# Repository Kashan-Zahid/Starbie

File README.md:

# Starbie

Starbie is a custom electronics project built around a designed PCB, firmware, and a 3D-printed enclosure. The project combines circuit design, component integration, embedded programming, and enclosure modelling into one compact device.

## Circuit Design

The circuit schematic and PCB layout were designed using KiCad. The schematic defines the electrical connections, while the PCB layout arranges the components and their connections on the board.

## Casing Design

I designed a custom 3D-printed enclosure to house and protect the electronics. The casing went through design revisions to improve its appearance and fit with the PCB.

## Why I Made It

I wanted to challenge myself to develop a hardware project from scratch and combine electronics, PCB design, firmware, and 3D modelling. This project gave me an opportunity to work through the process of turning a circuit design into a physical product.

## Features and Operation

- Custom PCB designed in KiCad.
- Electronic components integrated onto the board.
- Custom 3D-printed enclosure.
- Tactile buttons for user input.
- USB-C power connection, if supported by the final assembled design.

Refer to the final firmware and schematic for the exact functions supported by the completed device.

## Assembly Instructions

### 1. Review the design files

Open the KiCad schematic (`.kicad_sch`) and PCB layout (`.kicad_pcb`). Review the component positions, footprints, and electrical connections before assembly.

### 2. Prepare the PCB

Export the Gerber and drill files from KiCad if the board will be manufactured by a PCB fabrication service. Check the manufacturing outputs before submitting them.

### 3. Gather the components

Use the BOM to identify the required components, quantities, and package types. Confirm that each component matches the footprint and electrical specifications in the schematic.

### 4. Assemble the electronics

Place each component according to the PCB silkscreen, schematic, and component polarity markings. Solder the components that require soldering, checking for solder bridges and incorrect orientations.

### 5. Inspect the assembled board

Before applying power, inspect the solder joints and verify the power connections. Check for shorts between power and ground with a multimeter.

### 6. Install the firmware

Use the firmware files included in the repository and follow the programming instructions for the microcontroller used in the final design. Confirm that the firmware matches the hardware and required pin assignments.

### 7. Test the electronics

Power the board using its specified supply voltage. Test the display, sensors, buttons, and other connected components individually, then verify that they work together as intended.

### 8. Fit the enclosure

Place the tested PCB into the 3D-printed casing. Check the alignment of the display, buttons, connectors, and mounting points. Make any necessary adjustments before final assembly.

**Note:** These are general assembly steps. Exact soldering locations, firmware commands, pin assignments, and mounting instructions should be added from the final hardware and firmware files.

## Challenges I Faced

Designing the PCB and creating a casing that fits the electronics required careful planning and revisions. I improved the PCB layout after reviewing the earlier design and worked on redesigning the enclosure to achieve a better fit and appearance. Preparing manufacturing files also helped me understand how a digital PCB design becomes a physical board.

## What I Learned

- Designing electronic schematics and PCB layouts using KiCad.
- Organising components and checking footprints.
- Preparing PCB manufacturing files.
- Designing and revising a 3D-printed enclosure.
- Planning the integration of electronics, firmware, and physical components.

## Bill of Materials (BOM)

The following table lists the component prices previously recorded for the project. Prices and availability must be confirmed against the linked product listings before they are treated as verified current prices.

| Component | Quantity | Supplier | Unit price (USD) | Line total (USD) |
|---|---:|---|---:|---:|
| DHT11 temperature and humidity sensor | 1 | [Circuit.pk](https://circuit.pk/product/227) | $1.00 | $1.00 |
| OLED display | 1 | [Circuit.pk](https://circuit.pk/product/606) | $3.61 | $3.61 |
| MPU6500 motion sensor | 1 | [Circuit.pk](https://circuit.pk/product/4431) | $1.73 | $1.73 |
| Mechanical keyboard switches | 2 | [MegaTechMall](https://megatechmall.com/shop/electronic-devices/mechanical-keyboard-silent-switches-200pcs-dustproof-switches/) | $0.73 | $1.46 |
| 10 kΩ resistor | 1 | [Daraz.pk](https://www.daraz.pk/products/25-10k-ohm-14w-i186088466) | $0.16 | $0.16 |
| MB102 breadboard | 1 | [Digilog.pk](https://digilog.pk/products/mb102-830-points-solderless-prototype-pcb-breadboard-high-quality-in-pakistan) | $1.01 | $1.01 |
| **Component subtotal** | | | | **$8.97** |
| Shipping | — | Multiple suppliers | Not verified | Not verified |
| **Total** | | | | **$8.97 + actual shipping** |

The component subtotal is calculated from the recorded prices above; it is not a verified final purchase cost. The previous $6.00 shipping figure has not been independently confirmed and is therefore excluded from the total.

**Important:** The breadboard is a prototyping item, so confirm whether it belongs in the final project BOM or was only used during development. Also confirm that the listed components match the final PCB design.

See [`BOM.csv`](BOM.csv) for the component list.

## Editable 3D Design (Onshape)

The Starbie enclosure was designed using Onshape. I created and revised the 3D model to fit the electronics and provide a finished enclosure for the project.

The original editable CAD document is available here:

**[View Starbie's Editable 3D Design on Onshape](https://cad.onshape.com/documents/d6ad51c0185554a6a528b003/w/05fafd2a75e4a24dc14ee40b/e/c8ed782f1f7a7a6b0a75496d?renderMode=0&uiState=6ae42ee53693e84fc74a8607)**

The editable document allows others to inspect the original design and understand how the enclosure was modelled.

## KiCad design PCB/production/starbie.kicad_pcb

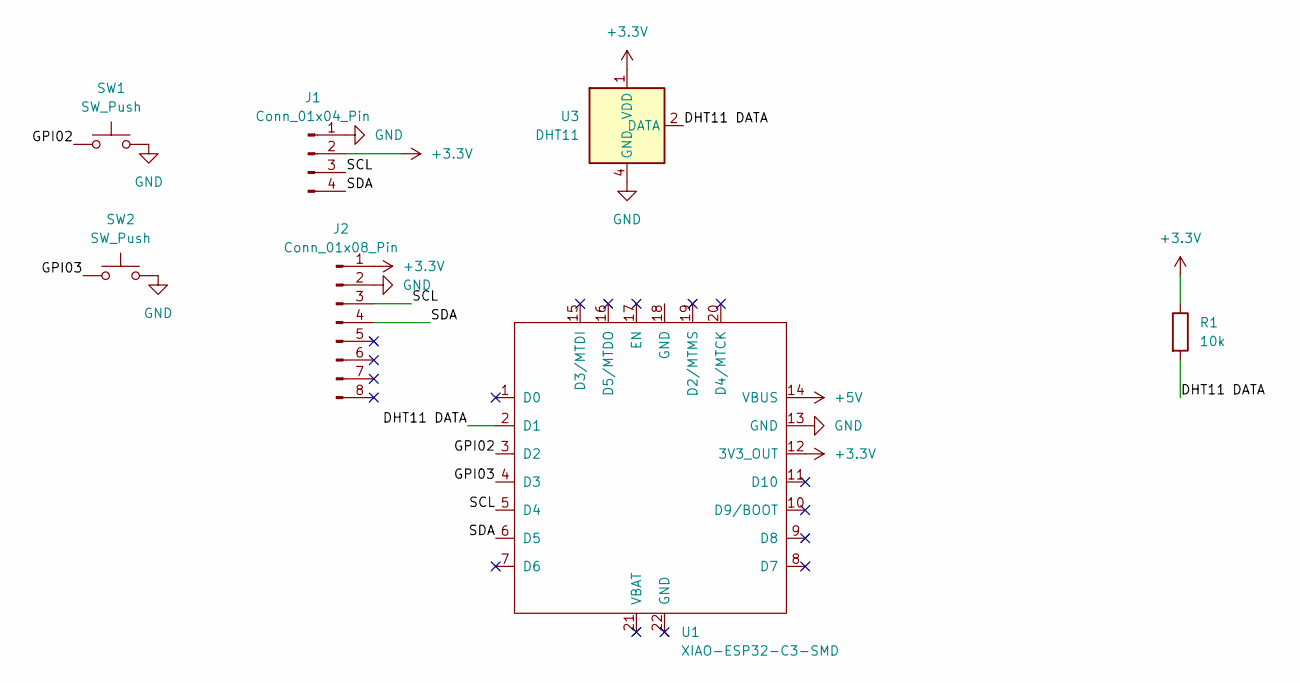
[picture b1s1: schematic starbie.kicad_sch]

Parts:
J1: Conn_01x04_Pin; Display_128x64_096_I2C
J2: Conn_01x08_Pin; MPU6050_Module
R1: 10k; R_Axial_DIN0204_L3.6mm_D1.6mm_P7.62mm_Horizontal
SW1, SW2: SW_Push; SW_Cherry_MX_1.00u_PCB
U1: XIAO-ESP32-C3-SMD; MCU_Seeed_ESP32C3
U3: DHT11; Aosong_DHT11_5.5x12.0_P2.54mm

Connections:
+3.3V: J1.2, J2.1, R1.1, U1.12 (3V3_OUT), U3.1 (VDD)
+5V: U1.14 (VBUS)
/DHT11 DATA: R1.2, U1.2 (D1), U3.2 (DATA)
/GPI02: SW1.1, U1.3 (D2)
/GPI03: SW2.1, U1.4 (D3)
/SCL: J1.3, J2.3, U1.5 (D4)
/SDA: J1.4, J2.4, U1.6 (D5)
GND: J1.1, J2.2, SW1.2, SW2.2, U1.13 (GND), U3.4 (GND)

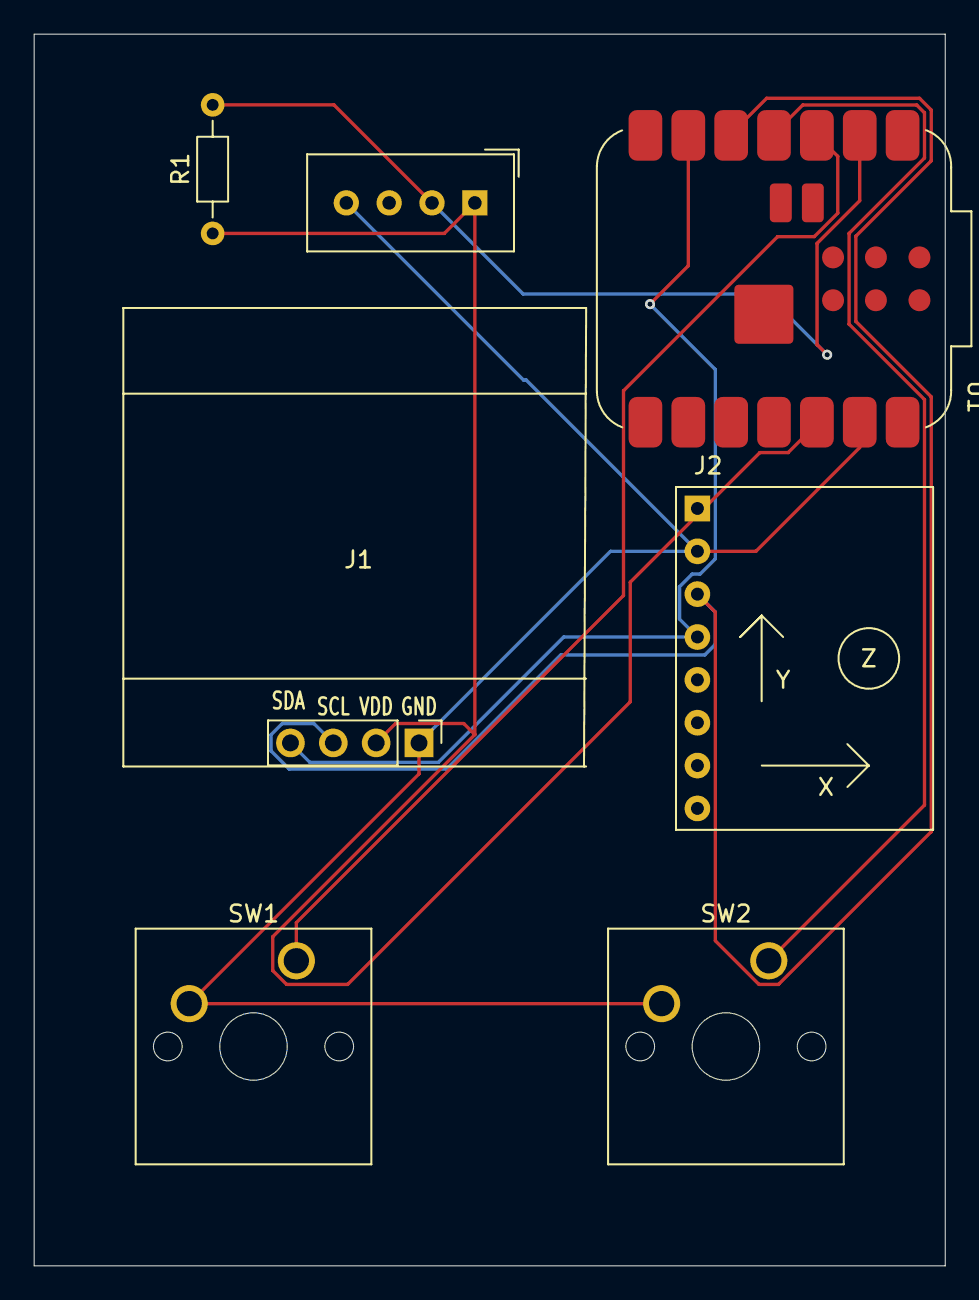
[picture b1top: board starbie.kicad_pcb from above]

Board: 2 copper layers, 54.0 x 73.0 mm, 7 parts (0 on the bottom side), 7 nets.
